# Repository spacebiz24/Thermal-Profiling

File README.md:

# Thermal Profiling on Fabrics

This repository is divided into the following sections:

```mermaid
graph TD;
Repo --> Dashboard
Repo --> Documentation
Repo --> Firmware
Repo --> Hardware
Repo --> Thermoscope
```

Each section explains more about itself in its own `README.md` file. Please look into them.
___
Made with :heart: by [spacebiz24](https://github.com/spacebiz24), [dkoppad3](https://github.com/dkoppad3), [DivakarGC](https://github.com/DivakarGC), [naruto4526](https://github.com/naruto4526), [Eloquencere](https://github.com/Eloquencere), [Tejas-M-Nayak](https://github.com/Tejas-M-Nayak) and [L-o-n-e-W-o-l-f](https://github.com/L-o-n-e-W-o-l-f)

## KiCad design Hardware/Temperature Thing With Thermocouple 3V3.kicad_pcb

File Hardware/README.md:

# Hardware
This directory contains all the files concerning the project hardware, including the PCB and the overall casing.

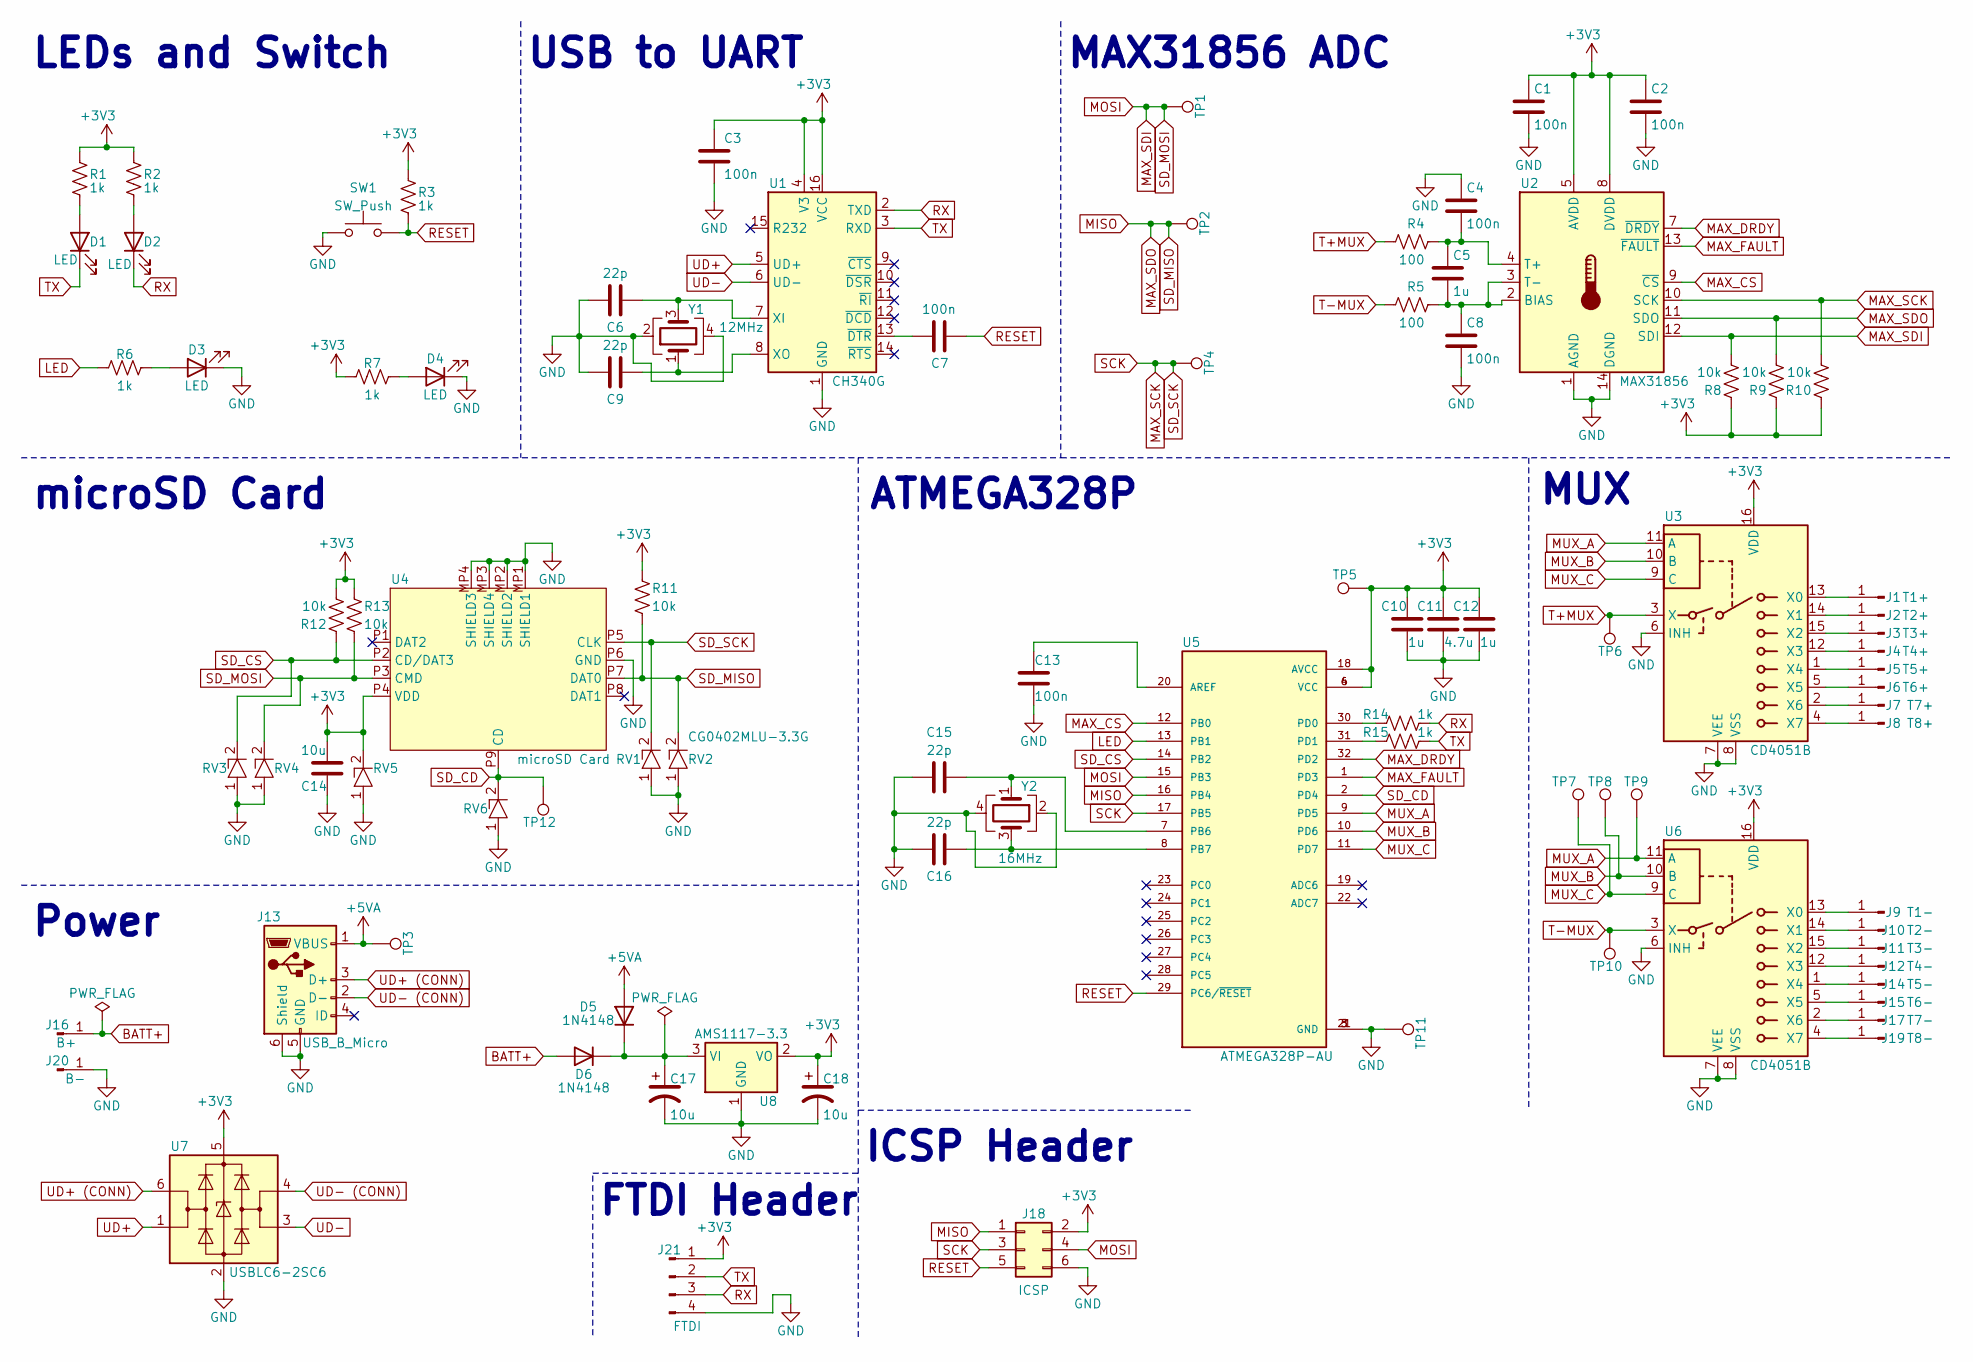
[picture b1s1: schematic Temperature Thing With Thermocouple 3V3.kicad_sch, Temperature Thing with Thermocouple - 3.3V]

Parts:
C1, C2, C3, C4, C7, C8, C13: 100n; C_0603_1608Metric
C5, C10, C12: 1u; C_0603_1608Metric
C6, C9, C15, C16: 22p; C_0603_1608Metric
C11: 4.7u; C_0603_1608Metric
C14, C17, C18: 10u; C_0603_1608Metric
D1, D2, D3, D4: LED; LED_0603_1608Metric
D5, D6: 1N4148; D_SOD-123
J1: T1+; M2-Plated-Hole
J2: T2+; M2-Plated-Hole
J3: T3+; M2-Plated-Hole
J4: T4+; M2-Plated-Hole
J5: T5+; M2-Plated-Hole
J6: T6+; M2-Plated-Hole
J7: T7+; M2-Plated-Hole
J8: T8+; M2-Plated-Hole
J9: T1-; M2-Plated-Hole
J10: T2-; M2-Plated-Hole
J11: T3-; M2-Plated-Hole
J12: T4-; M2-Plated-Hole
J13: USB_B_Micro; XKB-micro-USB
J14: T5-; M2-Plated-Hole
J15: T6-; M2-Plated-Hole
J16: B+; PinSocket_1x01_P2.54mm_Vertical
J17: T7-; M2-Plated-Hole
J18: ICSP; PinHeader_2x03_P2.54mm_Vertical
J19: T8-; M2-Plated-Hole
J20: B-; PinSocket_1x01_P2.54mm_Vertical
J21: FTDI; PinHeader_1x04_P2.54mm_Vertical
R1, R2, R3, R6, R7, R14, R15: 1k; R_0603_1608Metric
R4, R5: 100; R_0603_1608Metric
R8, R9, R10, R11, R12, R13: 10k; R_0603_1608Metric
RV1, RV2, RV3, RV4, RV5, RV6: CG0402MLU-3.3G; CG402MLU-3_3G; Mouser Part Number 652-CG0402MLU-3.3G
SW1: SW_Push; SW_SPST_CK_RS282G05A3
TP1, TP2, TP3, TP4, TP5, TP6, TP7, TP8, TP9, TP10, TP11, TP12: TestPoint_Pad_1.0x1.0mm
U1: CH340G; SOIC-16_3.9x9.9mm_P1.27mm
U2: MAX31856; TSSOP-14_4.4x5mm_P0.65mm
U3, U6: CD4051B; CD4051BPWR
U4: microSD Card; GCT-MICROSD-HOLDER
U5: ATMEGA328P-AU
U7: USBLC6-2SC6; SOT-23-6
U8: AMS1117-3.3; SOT-223-3_TabPin2
Y1: 12MHz; Crystal_SMD_3225-4Pin_3.2x2.5mm
Y2: 16MHz; Crystal_SMD_3225-4Pin_3.2x2.5mm

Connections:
+3V3: C1.1, C2.1, C3.2, C10.2, C11.2, C12.2, C14.1, C18.1, J18.2, J21.1, R1.1, R2.1, R3.1, R7.1, R8.1, R9.1, R10.1, R11.1, R12.2, R13.1, RV5.2, TP5.1, U1.4 (V3), U1.16 (VCC), U2.5 (AVDD), U2.8 (DVDD), U3.16 (VDD), U4.P4 (VDD), U5.4 (VCC), U5.6 (VCC), U5.18 (AVCC), U6.16 (VDD), U7.5 (VBUS), U8.2 (VO)
+5VA: D5.2 (A), J13.1 (VBUS), TP3.1
BATT+: D6.2 (A), J16.1
GND: C1.2, C2.2, C3.1, C4.1, C6.1, C8.2, C9.1, C10.1, C11.1, C12.1, C13.1, C14.2, C15.1, C16.1, C17.2, C18.2, D3.1 (K), D4.1 (K), J13.5 (GND), J13.6 (Shield), J18.6, J20.1, J21.4, RV1.1, RV2.1, RV3.1, RV4.1, RV5.1, RV6.1, SW1.1, TP11.1, U1.1 (GND), U2.1 (AGND), U2.14 (DGND), U3.6 (INH), U3.7 (VEE), U3.8 (VSS), U4.MP1 (SHIELD1), U4.MP2 (SHIELD2), U4.MP3 (SHIELD4), U4.MP4 (SHIELD3), U4.P6 (GND), U5.3 (GND), U5.5 (GND), U5.21 (GND), U6.6 (INH), U6.7 (VEE), U6.8 (VSS), U7.2 (GND), U8.1 (GND), Y1.2, Y1.4, Y2.2, Y2.4
LED: R6.2, U5.13 (PB1)
MAX_CS: U2.9 (~CS), U5.12 (PB0)
MAX_DRDY: U2.7 (~DRDY), U5.32 (PD2)
MAX_FAULT: U2.13 (~FAULT), U5.1 (PD3)
MAX_SCK: J18.3, R10.2, RV1.2, TP4.1, U2.10 (SCK), U4.P5 (CLK), U5.17 (PB5)
MAX_SDI: J18.4, R8.2, R13.2, RV4.2, TP1.1, U2.12 (SDI), U4.P3 (CMD), U5.15 (PB3)
MAX_SDO: J18.1, R9.2, R11.2, RV2.2, TP2.1, U2.11 (SDO), U4.P7 (DAT0), U5.16 (PB4)
MUX_A: TP9.1, U3.11 (A), U5.9 (PD5), U6.11 (A)
MUX_B: TP8.1, U3.10 (B), U5.10 (PD6), U6.10 (B)
MUX_C: TP7.1, U3.9 (C), U5.11 (PD7), U6.9 (C)
unnamed: C17.1, D5.1 (K), D6.1 (K), U8.3 (VI)
unnamed: D1.2 (A), R1.2
unnamed: D2.2 (A), R2.2
unnamed: D3.2 (A), R6.1
unnamed: D4.2 (A), R7.2
unnamed: J1.1, U3.13 (X0)
unnamed: J2.1, U3.14 (X1)
unnamed: J3.1, U3.15 (X2)
unnamed: J4.1, U3.12 (X3)
unnamed: J5.1, U3.1 (X4)
unnamed: J6.1, U3.5 (X5)
unnamed: J7.1, U3.2 (X6)
unnamed: J8.1, U3.4 (X7)
unnamed: J9.1, U6.13 (X0)
unnamed: J10.1, U6.14 (X1)
unnamed: J11.1, U6.15 (X2)
unnamed: J12.1, U6.12 (X3)
unnamed: J14.1, U6.1 (X4)
unnamed: J15.1, U6.5 (X5)
unnamed: J17.1, U6.2 (X6)
unnamed: J19.1, U6.4 (X7)
unnamed: C6.2, U1.7 (XI), Y1.3
unnamed: C9.2, U1.8 (XO), Y1.1
unnamed: C7.1, U1.13 (~DTR)
unnamed: C5.2, C8.1, R5.2, U2.2 (BIAS), U2.3 (T-)
unnamed: C4.2, C5.1, R4.2, U2.4 (T+)
unnamed: C13.2, U5.20 (AREF)
unnamed: C15.2, U5.7 (PB6), Y2.1
unnamed: C16.2, U5.8 (PB7), Y2.3
unnamed: R14.2, U5.30 (PD0)
unnamed: R15.2, U5.31 (PD1)
RESET: C7.2, J18.5, R3.2, SW1.2, U5.29 (PC6/~RESET)
RX: D2.1 (K), J21.3, R14.1, U1.2 (TXD)
SD_CD: RV6.2, TP12.1, U4.P9 (CD), U5.2 (PD4)
SD_CS: R12.1, RV3.2, U4.P2 (CD/DAT3), U5.14 (PB2)
T+MUX: R4.1, TP6.1, U3.3 (X)
T-MUX: R5.1, TP10.1, U6.3 (X)
TX: D1.1 (K), J21.2, R15.1, U1.3 (RXD)
UD+: U1.5 (UD+), U7.1 (I/O1)
UD+ (CONN): J13.3 (D+), U7.6 (I/O1)
UD-: U1.6 (UD-), U7.3 (I/O2)
UD- (CONN): J13.2 (D-), U7.4 (I/O2)

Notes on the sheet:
USB to UART
ATMEGA328P
LEDs and Switch
MAX31856 ADC
ICSP Header
Power
FTDI Header
MUX
microSD Card

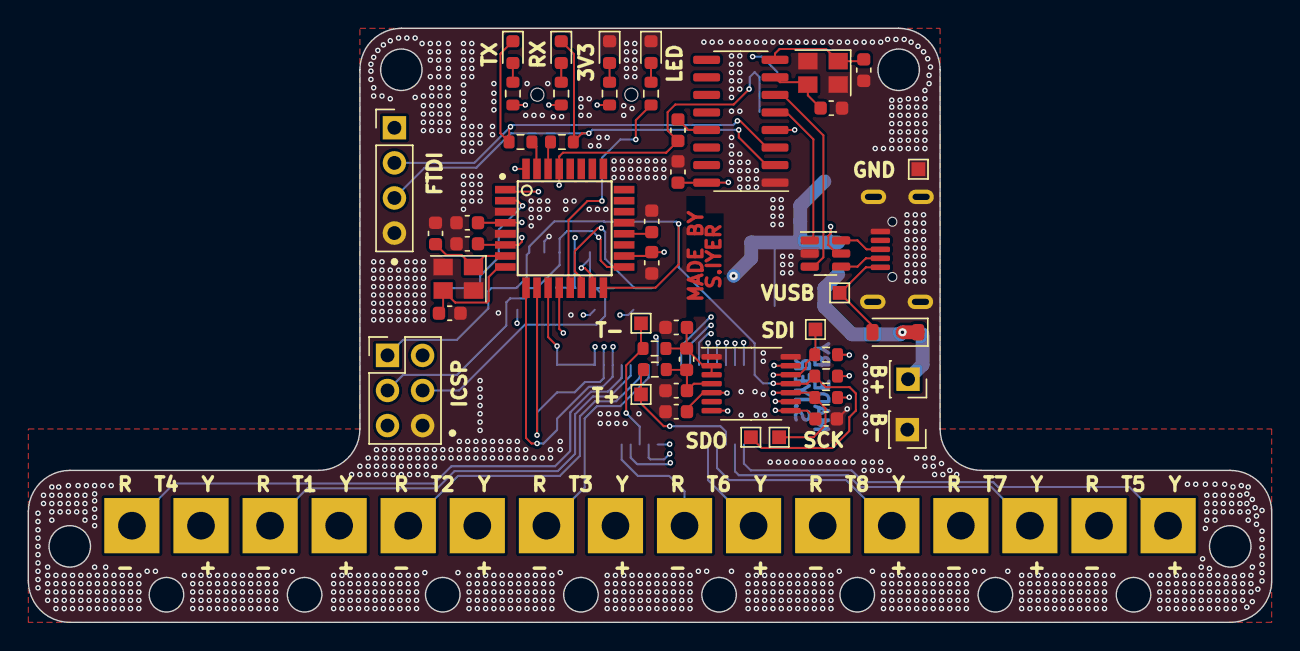
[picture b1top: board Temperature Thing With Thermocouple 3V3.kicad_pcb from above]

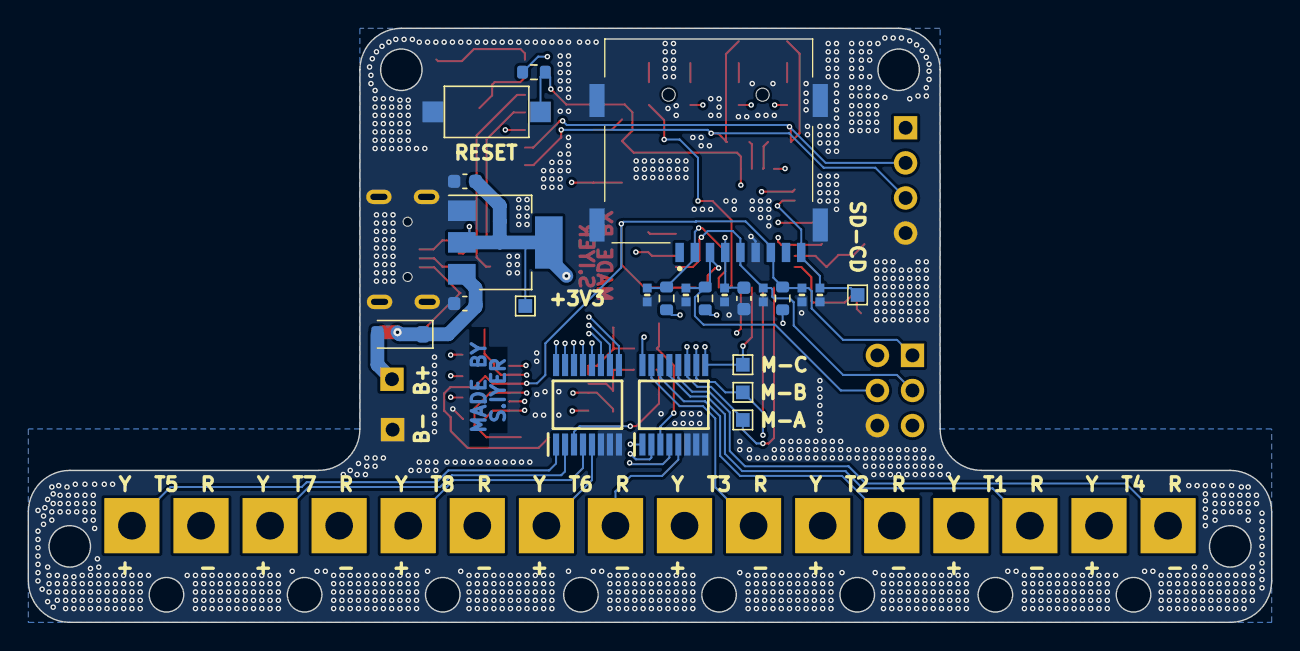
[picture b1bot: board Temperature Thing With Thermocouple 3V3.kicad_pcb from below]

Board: 4 copper layers, 90.0 x 43.0 mm, 89 parts (24 on the bottom side), 56 nets.

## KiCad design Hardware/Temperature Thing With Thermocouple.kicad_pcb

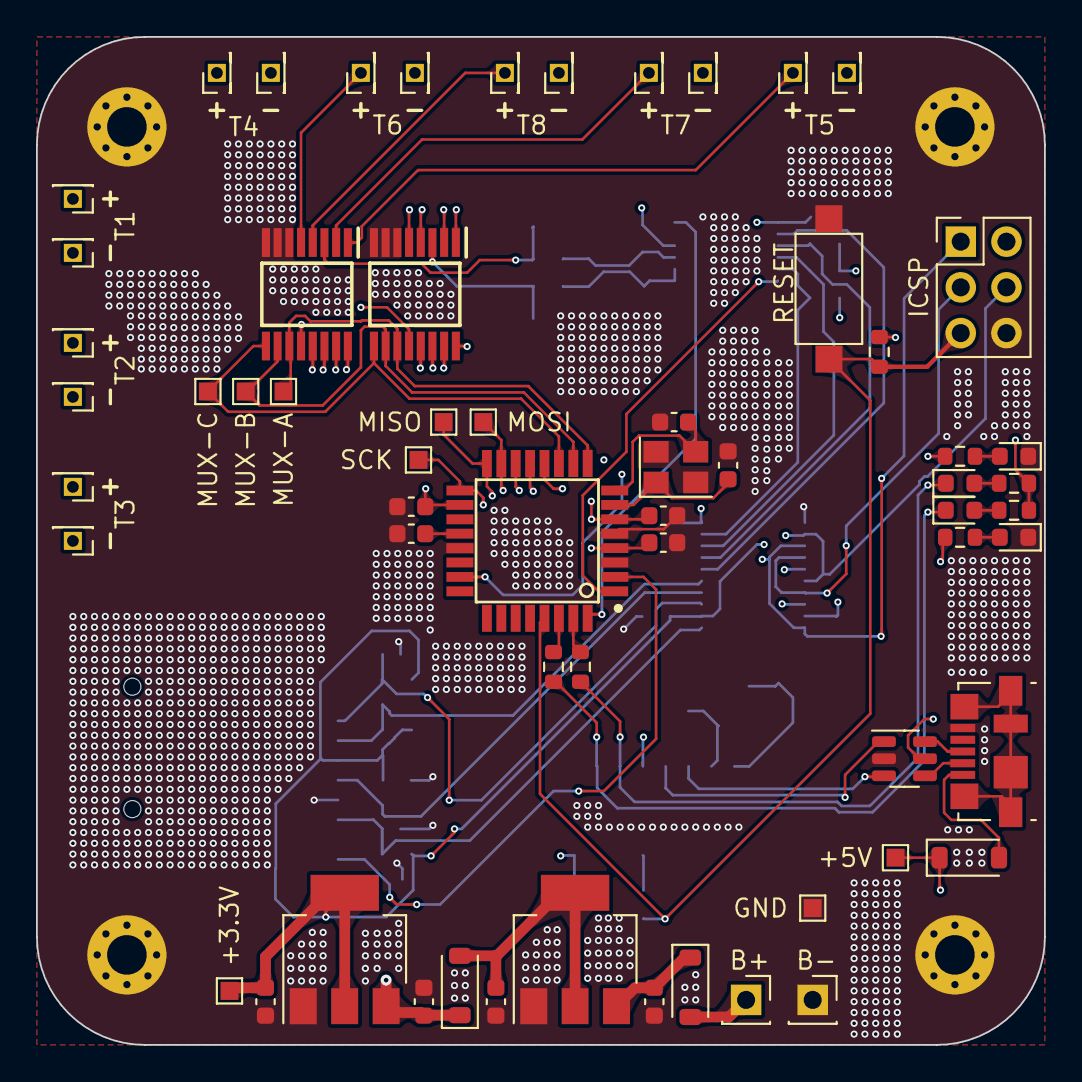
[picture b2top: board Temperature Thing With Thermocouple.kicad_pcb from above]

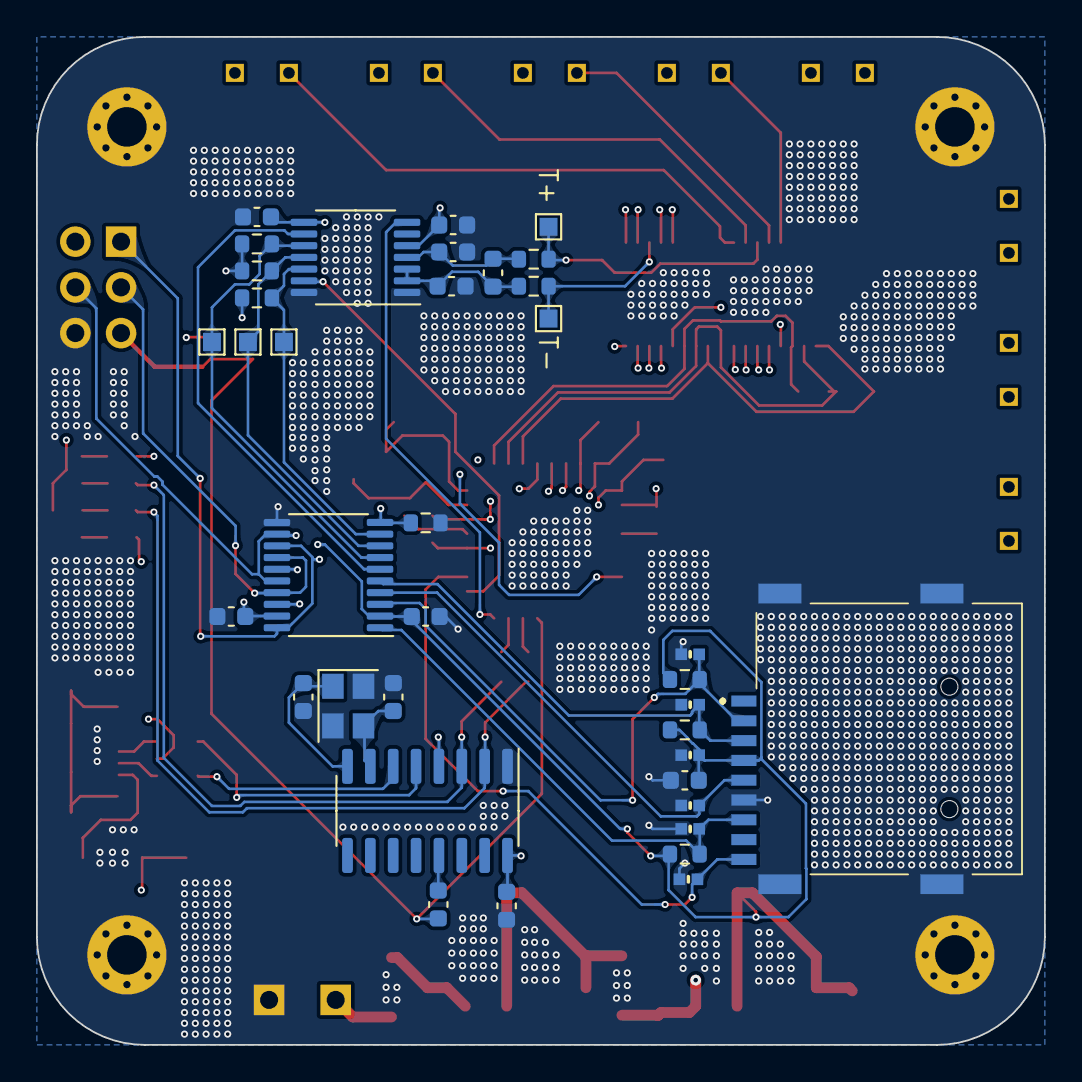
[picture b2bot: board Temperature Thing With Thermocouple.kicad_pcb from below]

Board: 4 copper layers, 56.0 x 56.0 mm, 102 parts (37 on the bottom side), 67 nets.

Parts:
C1, C2, C3, C4, C5, C7: 0.1u; C_0603_1608Metric
C6, C10: 0.01u; C_0603_1608Metric
C8, C11, C17, C18: 22p; C_0603_1608Metric
C9, C15: 100n; C_0603_1608Metric
C12, C14: 1u; C_0603_1608Metric
C13: 4.7u; C_0603_1608Metric
C16, C19, C20, C21, C22: 10u; C_0603_1608Metric
D1, D5, D6, D7: LED; LED_0603_1608Metric
D2, D3, D4: 1N4148; D_SOD-123
H1, H2, H3, H4: M2; MountingHole_2.2mm_M2_Pad_Via
J1: T1+; PinHeader_1x01_P1.27mm_Vertical
J2: T2+; PinHeader_1x01_P1.27mm_Vertical
J3: T3+; PinHeader_1x01_P1.27mm_Vertical
J4: T4+; PinHeader_1x01_P1.27mm_Vertical
J5: T5+; PinHeader_1x01_P1.27mm_Vertical
J6: T6+; PinHeader_1x01_P1.27mm_Vertical
J7: T7+; PinHeader_1x01_P1.27mm_Vertical
J8: T8+; PinHeader_1x01_P1.27mm_Vertical
J9: T1-; PinHeader_1x01_P1.27mm_Vertical
J10: T2-; PinHeader_1x01_P1.27mm_Vertical
J11: T3-; PinHeader_1x01_P1.27mm_Vertical
J12: T4-; PinHeader_1x01_P1.27mm_Vertical
J13: T5-; PinHeader_1x01_P1.27mm_Vertical
J14: T6-; PinHeader_1x01_P1.27mm_Vertical
J15: T7-; PinHeader_1x01_P1.27mm_Vertical
J16: T8-; PinHeader_1x01_P1.27mm_Vertical
J17: ICSP; PinHeader_2x03_P2.54mm_Vertical
J18: B+; PinSocket_1x01_P2.54mm_Vertical
J19: B-; PinSocket_1x01_P2.54mm_Vertical
J20: USB_B_Micro; USB_Micro-B_Molex_47346-0001
R1: 47k; R_0603_1608Metric
R2, R3: 100; R_0603_1608Metric
R4, R5, R6, R7, R8, R9: 10k; R_0603_1608Metric
R10, R11, R12, R13, R14, R15, R16: 1k; R_0603_1608Metric
RV1, RV2, RV3, RV4, RV5, RV6: CG0402MLU-3.3G; CG402MLU-3_3G
SW1: SW_Push; SW_SPST_CK_RS282G05A3
TP1, TP2, TP3, TP4, TP5, TP6, TP7, TP8, TP9, TP10, TP11, TP12, TP13, TP14: TestPoint_Pad_1.0x1.0mm
U1: CH340G; SOIC-16_3.9x9.9mm_P1.27mm
U2: MAX31856; TSSOP-14_4.4x5mm_P0.65mm
U3: TXS0108EPW; TSSOP-20_4.4x6.5mm_P0.65mm
U4, U8: CD4051B; CD4051BPWR
U5: microSD Card; GCT-MICROSD-HOLDER
U6: ATMEGA328P-AU
U7: AMS1117-3.3; SOT-223-3_TabPin2
U9: USBLC6-2SC6; SOT-23-6
U10: AMS1117-5.0; SOT-223-3_TabPin2
Y1: 12MHz; Crystal_SMD_3225-4Pin_3.2x2.5mm
Y2: 16MHz; Crystal_SMD_3225-4Pin_3.2x2.5mm

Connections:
+3V3: C1.1, C2.1, C3.1, C16.1, C20.1, R4.1, R5.1, R6.1, R7.1, R8.2, R9.1, RV5.2, TP1.1, U2.5 (AVDD), U2.8 (DVDD), U3.2 (VCCA), U5.P4 (VDD), U7.2 (VO)
+5V: C4.2, C5.1, C12.2, C13.2, C14.2, C19.1, D2.1 (K), D4.1 (K), J17.2, R13.1, R14.1, R15.1, R16.1, TP3.1, U1.4 (V3), U1.16 (VCC), U3.19 (VCCB), U4.16 (VDD), U6.4 (VCC), U6.6 (VCC), U6.18 (AVCC), U7.3 (VI), U8.16 (VDD), U9.5 (VBUS)
+5VA: D2.2 (A), J20.1 (VBUS)
BATT+: D3.2 (A), J18.1
GND: C1.2, C2.2, C3.2, C4.1, C5.2, C6.1, C8.1, C10.2, C11.1, C12.1, C13.1, C14.1, C15.1, C16.2, C17.1, C18.1, C19.2, C20.2, C21.2, C22.2, D1.1 (K), D5.1 (K), H1.1, H2.1, H3.1, H4.1, J17.6, J19.1, J20.5 (GND), R1.1, RV1.1, RV2.1, RV3.1, RV4.1, RV5.1, RV6.1, SW1.1, TP14.1, U1.1 (GND), U2.1 (AGND), U2.14 (DGND), U3.11 (GND), U4.6 (INH), U4.7 (VEE), U4.8 (VSS), U5.MP1 (SHIELD1), U5.MP2 (SHIELD2), U5.MP3 (SHIELD4), U5.MP4 (SHIELD3), U5.P6 (GND), U6.3 (GND), U6.5 (GND), U6.21 (GND), U7.1 (GND), U8.6 (INH), U8.7 (VEE), U8.8 (VSS), U9.2 (GND), U10.1 (GND), Y1.2, Y1.4, Y2.2, Y2.4
LED: R12.2, U6.13 (PB1)
MAX_CS: U3.15 (B5), U6.12 (PB0)
MAX_CS_C: U2.9 (~CS), U3.6 (A5)
MAX_DRDY: U2.7 (~DRDY), U6.32 (PD2)
MAX_FAULT: U2.13 (~FAULT), U6.1 (PD3)
MAX_SCK: J17.3, TP8.1, U3.14 (B6), U3.17 (B3), U6.17 (PB5)
MAX_SCK_C: R6.2, TP7.1, U2.10 (SCK), U3.7 (A6)
MAX_SDI: J17.4, TP2.1, U3.12 (B8), U3.16 (B4), U6.15 (PB3)
MAX_SDI_C: R4.2, TP5.1, U2.12 (SDI), U3.9 (A8)
MAX_SDO: J17.1, TP4.1, U3.13 (B7), U3.20 (B1), U6.16 (PB4)
MAX_SDO_C: R5.2, TP6.1, U2.11 (SDO), U3.8 (A7)
MUX_A: TP12.1, U4.11 (A), U6.9 (PD5), U8.11 (A)
MUX_B: TP11.1, U4.10 (B), U6.10 (PD6), U8.10 (B)
MUX_C: TP10.1, U4.9 (C), U6.11 (PD7), U8.9 (C)
unnamed: D1.2 (A), R12.1
unnamed: C21.1, D3.1 (K), U10.3 (VI)
unnamed: C22.1, D4.2 (A), U10.2 (VO)
unnamed: D5.2 (A), R15.2
unnamed: D6.2 (A), R13.2
unnamed: D7.2 (A), R14.2
unnamed: J1.1, U4.13 (X0)
unnamed: J2.1, U4.14 (X1)
unnamed: J3.1, U4.15 (X2)
unnamed: J4.1, U4.12 (X3)
unnamed: J5.1, U4.1 (X4)
unnamed: J6.1, U4.5 (X5)
unnamed: J7.1, U4.2 (X6)
unnamed: J8.1, U4.4 (X7)
unnamed: J9.1, U8.13 (X0)
unnamed: J10.1, U8.14 (X1)
unnamed: J11.1, U8.15 (X2)
unnamed: J12.1, U8.12 (X3)
unnamed: J13.1, U8.1 (X4)
unnamed: J14.1, U8.5 (X5)
unnamed: J15.1, U8.2 (X6)
unnamed: J16.1, U8.4 (X7)
unnamed: C8.2, U1.7 (XI), Y1.3
unnamed: C11.2, U1.8 (XO), Y1.1
unnamed: C9.1, U1.13 (~DTR)
unnamed: C7.2, C10.1, R3.2, U2.2 (BIAS), U2.3 (T-)
unnamed: C6.2, C7.1, R2.2, U2.4 (T+)
unnamed: C15.2, U6.20 (AREF)
unnamed: C17.2, U6.7 (PB6), Y2.1
unnamed: C18.2, U6.8 (PB7), Y2.3
unnamed: R10.2, U6.30 (PD0)
unnamed: R11.2, U6.31 (PD1)
OE: R1.2, U3.10 (OE), U6.23 (PC0)
RESET: C9.2, J17.5, R16.2, SW1.2, U6.29 (PC6/~RESET)
RX: D7.1 (K), R10.1, U1.2 (TXD)
SD_CD: RV6.2, U5.P9 (CD), U6.2 (PD4)
SD_CLK_C: RV1.2, U3.4 (A3), U5.P5 (CLK)
SD_CS: U3.18 (B2), U6.14 (PB2)
SD_CS_C: R8.1, RV3.2, U3.3 (A2), U5.P2 (CD/DAT3)
SD_MISO_C: R7.2, RV2.2, U3.1 (A1), U5.P7 (DAT0)
SD_MOSI_C: R9.2, RV4.2, U3.5 (A4), U5.P3 (CMD)
T+MUX: R2.1, TP9.1, U4.3 (X)
T-MUX: R3.1, TP13.1, U8.3 (X)
TX: D6.1 (K), R11.1, U1.3 (RXD)
UD+: U1.5 (UD+), U9.1 (I/O1)
UD+ (CONN): J20.3 (D+), U9.6 (I/O1)
UD-: U1.6 (UD-), U9.3 (I/O2)
UD- (CONN): J20.2 (D-), U9.4 (I/O2)

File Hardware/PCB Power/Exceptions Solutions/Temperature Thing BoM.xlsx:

# | Reference | Qty | Value | Footprint | Link
1.0 | C1, C2, C3, C4, C5, C7 | 6.0 | 0.1u | Capacitor_SMD:C_0603_1608Metric | Robu
2.0 | C6, C10 | 2.0 | 0.01u | Capacitor_SMD:C_0603_1608Metric | Robu
3.0 | C8, C11, C17, C18 | 4.0 | 22p | Capacitor_SMD:C_0603_1608Metric | Robu
4.0 | C9, C15 | 2.0 | 100n | Capacitor_SMD:C_0603_1608Metric | Robu
5.0 | C12, C14 | 2.0 | 1u | Capacitor_SMD:C_0603_1608Metric | Robu
6.0 | C13 | 1.0 | 4.7u | Capacitor_SMD:C_0603_1608Metric | Robu
7.0 | C16, C19, C20, C21, C22 | 5.0 | 10u | Capacitor_SMD:C_0603_1608Metric | Evelta
8.0 | D1, D5, D6, D7 | 4.0 | LED | LED_SMD:LED_0603_1608Metric | Evelta
9.0 | D2, D3, D4 | 3.0 | 1N4148 | Diode_SMD:D_SOD-123 | Evelta
10.0 | J17 | 1.0 | Pin Header | PinHeader_2x03_P2.54mm_Vertical | Robu
11.0 | J20 | 1.0 | USB_B_Micro | Connector_USB:USB_Micro-B_Molex_47346-0001 | Robu
12.0 | R1, R2 | 2.0 | 100.0 | Resistor_SMD:R_0603_1608Metric | Robu
13.0 | R3, R4, R5, R6, R7, R8 | 6.0 | 10k | Resistor_SMD:R_0603_1608Metric | Robu
14.0 | R9, R10, R11, R12, R13, R14, R15 | 7.0 | 1k | Resistor_SMD:R_0603_1608Metric | Robu
15.0 | RV1, RV2, RV3, RV4, RV5, RV6 | 6.0 | CG0402MLU-3.3G | CG402MLU-3_3G:CG402MLU-3_3G_0402 | Mouser
16.0 | SW1 | 1.0 | SW_Push | Button_Switch_SMD:SW_SPST_CK_RS282G05A3 | Robu
17.0 | U1 | 1.0 | CH340G | Package_SO:SOIC-16_3.9x9.9mm_P1.27mm | Robu
18.0 | U2 | 1.0 | TXS0108EPW | Package_SO:TSSOP-20_4.4x6.5mm_P0.65mm | Mouser
19.0 | U3 | 1.0 | MAX31856 | Package_SO:TSSOP-14_4.4x5mm_P0.65mm | Mouser
20.0 | U4, U8 | 2.0 | CD4051B | CD4051BPWR:CD4051BPWR_TSSOP-16-5x6.4mm | Mouser
21.0 | U5 | 1.0 | microSD Card | GCT-MICROSD-HOLDER:GCT-MICROSD-HOLDER | Mouser
22.0 | U6 | 1.0 | ATMEGA328P-AU | ATMEGA328P-AU:ATMEGA328P-AU - TQFP-32 | Robu
23.0 | U7 | 1.0 | AMS1117-3.3 | Package_TO_SOT_SMD:SOT-223-3_TabPin2 | Robu
24.0 | U9 | 1.0 | USBLC6-2SC6 | Package_TO_SOT_SMD:SOT-23-6 | Mouser
25.0 | U10 | 1.0 | AMS1117-5.0 | Package_TO_SOT_SMD:SOT-223-3_TabPin2 | Robu
26.0 | Y1 | 1.0 | 12MHz | Crystal:Crystal_SMD_3225-4Pin_3.2x2.5mm | Robu
27.0 | Y2 | 1.0 | 16MHz | Crystal:Crystal_SMD_3225-4Pin_3.2x2.5mm | Robu

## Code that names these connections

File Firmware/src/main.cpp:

//=================================================================
//
// Copyright (c) 2024 by Siddhaanth S Iyer. All rights reserved.
//
// This material may not be reproduced, displayed, modified or
// distributed without the express prior written permission of the
// copyright holder. For permission, contact Siddhaanth S Iyer.
//
//=================================================================
//
//=======================================
// !!!!!!!!!!! Please read the README.md
// file before coming here !!!!!!!!!!!!!
//=======================================

#include <Arduino.h>
#include <MAX31856.h>
#include <SdFat.h>

#define LED_PIN 9
#define MUX_PIN_A 5
#define MUX_PIN_B 6	
#define MUX_PIN_C 7
#define MAX_CS 8
#define SD_CS 10
#define SD_CD 4
#define MAX_FAULT 3
#define MAX_DATA_READY 2

#define SWITCHING_DELAY_MS 220
#define NUM_THERMOCOUPLES 8

const int BOARD_PINS[] = {LED_PIN, MAX_CS, SD_CS, SD_CD, MAX_FAULT, MAX_DATA_READY};
const int BOARD_PIN_DIR[] = {OUTPUT, OUTPUT, OUTPUT, INPUT, INPUT, INPUT};
const int MUX_PINS[] = {MUX_PIN_A, MUX_PIN_B, MUX_PIN_C};

double ColdJunctionTemp;
double ThermocoupleTemp[NUM_THERMOCOUPLES];
unsigned int timeStamp;

MAX31856 MAX;
SdFat SD;
File dataFile;

/**
 * \brief Function to indicate any failure
 * \param None
 * \return None
 */
void showFailure()
{
	digitalWrite(LED_PIN, HIGH);
	delay(250);
	digitalWrite(LED_PIN, LOW);
	delay(250);
}

/**
 * \brief Function to indicate successful initialisation
 * \param None
 * \return None
 */
void showSuccess()
{
	digitalWrite(LED_PIN, HIGH);
	delay(1000);
	digitalWrite(LED_PIN, LOW);
	delay(1000);
}

/**
 * \brief Function to select a specific MUX pin
 * \param Pin_Number The pin to be selected (0-7)
 * \return None
 */
void selectPin(int Pin_Number)
{
	for (int Pin = 0; Pin < 3; Pin++)
		digitalWrite(MUX_PINS[Pin], (Pin_Number & (1 << Pin)) != 0);
}

/**
 * \brief Function to read a single thermocouple
 * \param Thermocouple_Number The pin number of the thermocouple to be read (1-8)
 * \return None
 */
void readSingleThermocouple(int Thermocouple_Number)
{
	selectPin(Thermocouple_Number - 1);
	delay(SWITCHING_DELAY_MS);
	ThermocoupleTemp[Thermocouple_Number - 1] = MAX.readThermocoupleTemperature();
}

/**
 * \brief Function to cycle through all thermocouples
 * \param None
 * \return None
 */
void cycleThroughThermocouples()
{
	digitalWrite(LED_PIN, HIGH);
	for (int i = 1; i <= NUM_THERMOCOUPLES; i++)
		readSingleThermocouple(i);

	ColdJunctionTemp = MAX.readCJTemperature();
	Serial.print(timeStamp);
	Serial.print(",");
	for (int i = 0; i < NUM_THERMOCOUPLES; i++)
	{
		Serial.print(ThermocoupleTemp[i]);
		Serial.print(",");
	}
	Serial.println(ColdJunctionTemp);
	digitalWrite(LED_PIN, LOW);
}

/// \brief Setup Function
void setup()
{
	for (int i = 0; i < int(sizeof(BOARD_PINS) / sizeof(int)); i++)
		pinMode(BOARD_PINS[i], BOARD_PIN_DIR[i]);
	for (int i = 0; i < 3; i++)
		pinMode(MUX_PINS[i], OUTPUT);
	delayMicroseconds(10);
	Serial.begin(9600);
	digitalWrite(MAX_CS, HIGH);
	digitalWrite(SD_CS, HIGH);
	SD.begin(SD_CS);
	SD.remove("data.txt");
	SD.end();
}

/// \brief Loop Function
void loop()
{
	delay(1);
	digitalWrite(SD_CS, HIGH);
	MAX.begin(MAX_CS);
	timeStamp = millis() / 1000;
	cycleThroughThermocouples();
	delay(1);
	digitalWrite(MAX_CS, HIGH);
	SD.begin(SD_CS);
	dataFile = SD.open("data.txt", FILE_WRITE);
	if (dataFile)
	{
		dataFile.print(timeStamp);
		dataFile.print(",");
		for (int i = 0; i < NUM_THERMOCOUPLES; i++)
		{
			dataFile.print(ThermocoupleTemp[i]);
			dataFile.print(",");
		}
		dataFile.println(ColdJunctionTemp);
		dataFile.close();
	}
	SD.end();
}

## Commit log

2024-04-07 Create troubleshooting-device
    GUI-component for troubleshooting
2024-04-07 Added entire GUI files
    Uploaded directly
2024-07-12 Create LICENSE
2024-07-16 Bump pillow from 9.4.9 to 10.3.0 in /SDA-troubleshooting-device
    Bumps [pillow](https://github.com/python-pillow/Pillow) from 9.4.9 to 10.3.0.
    - [Release notes](https://github.com/python-pillow/Pillow/releases)
    - [Changelog](https://github.com/python-pillow/Pillow/blob/main/CHANGES.rst)
    - [Commits](https://github.com/python-pillow/Pillow/commits/10.3.0)
    ---
    updated-dependencies:
2024-12-09 Create Thermoscope
2024-12-09 Bump cross-spawn from 7.0.3 to 7.0.6 in /Thermoscope/Source Code
    Bumps [cross-spawn](https://github.com/moxystudio/node-cross-spawn) from 7.0.3 to 7.0.6.
    - [Changelog](https://github.com/moxystudio/node-cross-spawn/blob/master/CHANGELOG.md)
    - [Commits](https://github.com/moxystudio/node-cross-spawn/compare/v7.0.3...v7.0.6)
    ---
    updated-dependencies:
    - dependency-name: cross-spawn
2024-12-09 Bump micromatch from 4.0.7 to 4.0.8 in /Thermoscope/Source Code
    Bumps [micromatch](https://github.com/micromatch/micromatch) from 4.0.7 to 4.0.8.
    - [Release notes](https://github.com/micromatch/micromatch/releases)
    - [Changelog](https://github.com/micromatch/micromatch/blob/master/CHANGELOG.md)
    - [Commits](https://github.com/micromatch/micromatch/compare/4.0.7...4.0.8)
    ---
    updated-dependencies:
2024-12-09 Bump react-native-mmkv from 2.6.0 to 2.11.0 in /Thermoscope/Source Code
    Bumps [react-native-mmkv](https://github.com/mrousavy/react-native-mmkv) from 2.6.0 to 2.11.0.
    - [Release notes](https://github.com/mrousavy/react-native-mmkv/releases)
    - [Commits](https://github.com/mrousavy/react-native-mmkv/compare/v2.6.0...v2.11.0)
    ---
    updated-dependencies:
    - dependency-name: react-native-mmkv
2024-12-09 Bump fast-xml-parser from 4.4.0 to 4.5.0 in /Thermoscope/Source Code
    Bumps [fast-xml-parser](https://github.com/NaturalIntelligence/fast-xml-parser) from 4.4.0 to 4.5.0.
    - [Release notes](https://github.com/NaturalIntelligence/fast-xml-parser/releases)
    - [Changelog](https://github.com/NaturalIntelligence/fast-xml-parser/blob/master/CHANGELOG.md)
    - [Commits](https://github.com/NaturalIntelligence/fast-xml-parser/compare/v4.4.0...v4.5.0)
    ---
    updated-dependencies:
2024-12-09 Bump send and serve-static in /Thermoscope/Source Code
    Bumps [send](https://github.com/pillarjs/send) and [serve-static](https://github.com/expressjs/serve-static). These dependencies needed to be updated together.
    Updates `send` from 0.18.0 to 0.19.0
    - [Release notes](https://github.com/pillarjs/send/releases)
    - [Changelog](https://github.com/pillarjs/send/blob/master/HISTORY.md)
    - [Commits](https://github.com/pillarjs/send/compare/0.18.0...0.19.0)
    Updates `serve-static` from 1.15.0 to 1.16.2
2024-12-18 Bump nanoid from 3.3.7 to 3.3.8 in /Thermoscope/Source Code
    Bumps [nanoid](https://github.com/ai/nanoid) from 3.3.7 to 3.3.8.
    - [Release notes](https://github.com/ai/nanoid/releases)
    - [Changelog](https://github.com/ai/nanoid/blob/main/CHANGELOG.md)
    - [Commits](https://github.com/ai/nanoid/compare/3.3.7...3.3.8)
    ---
    updated-dependencies:
2025-05-25 Bump image-size from 1.1.1 to 1.2.1 in /Thermoscope/Source Code
    Bumps [image-size](https://github.com/image-size/image-size) from 1.1.1 to 1.2.1.
    - [Release notes](https://github.com/image-size/image-size/releases)
    - [Commits](https://github.com/image-size/image-size/compare/v1.1.1...v1.2.1)
    ---
    updated-dependencies:
    - dependency-name: image-size
2025-09-10 Bump @babel/runtime from 7.24.7 to 7.28.4 in /Thermoscope/Source Code
    Bumps [@babel/runtime](https://github.com/babel/babel/tree/HEAD/packages/babel-runtime) from 7.24.7 to 7.28.4.
    - [Release notes](https://github.com/babel/babel/releases)
    - [Changelog](https://github.com/babel/babel/blob/main/CHANGELOG.md)
    - [Commits](https://github.com/babel/babel/commits/v7.28.4/packages/babel-runtime)
    ---
    updated-dependencies:
2025-11-09 Bump @react-native-community/cli and react-native
    Removes [@react-native-community/cli](https://github.com/react-native-community/cli/tree/HEAD/packages/cli). It's no longer used after updating ancestor dependency [react-native](https://github.com/f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
    Removes `@react-native-community/cli`
    Updates `react-native` from 0.74.3 to 0.82.1
    - [Release notes](https://github.com/facebook/react-native/releases)
    - [Changelog](https://github.com/facebook/react-native/blob/main/CHANGELOG-0.7x.md)
    - [Commits](https://github.com/facebook/react-native/commits/v0.82.1/packages/react-native)
2025-12-29 Bump js-yaml in /Thermoscope/Source Code
    Bumps and [js-yaml](https://github.com/nodeca/js-yaml). These dependencies needed to be updated together.
    Updates `js-yaml` from 3.14.1 to 3.14.2
    - [Changelog](https://github.com/nodeca/js-yaml/blob/master/CHANGELOG.md)
    - [Commits](https://github.com/nodeca/js-yaml/compare/3.14.1...3.14.2)
    Updates `js-yaml` from 4.1.0 to 4.1.1
    - [Changelog](https://github.com/nodeca/js-yaml/blob/master/CHANGELOG.md)
2026-02-20 Bump pillow from 10.3.0 to 12.1.1 in /Dashboard/Version 2
    Bumps [pillow](https://github.com/python-pillow/Pillow) from 10.3.0 to 12.1.1.
    - [Release notes](https://github.com/python-pillow/Pillow/releases)
    - [Changelog](https://github.com/python-pillow/Pillow/blob/main/CHANGES.rst)
    - [Commits](https://github.com/python-pillow/Pillow/compare/10.3.0...12.1.1)
    ---
    updated-dependencies:
2026-02-20 Bump lodash from 4.17.21 to 4.17.23 in /Thermoscope/Source Code
    Bumps [lodash](https://github.com/lodash/lodash) from 4.17.21 to 4.17.23.
    - [Release notes](https://github.com/lodash/lodash/releases)
    - [Commits](https://github.com/lodash/lodash/compare/4.17.21...4.17.23)
    ---
    updated-dependencies:
    - dependency-name: lodash
